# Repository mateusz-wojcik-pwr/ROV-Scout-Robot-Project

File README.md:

# ROV-Scout-Robot-Project
Projekt mobilnego robota zwiadowczego typu ROV realizowany przez studentów kierunku Automatyka i Robotyka na Politechnice Wrocławskiej. Zespół projektowy: Zuzanna Kunikowska, Mateusz Wójcik

# Elektronika
### __Status ukończenia: 70%__
Poniższa sekcja zawiera informacje na temat elektronicznej części projektu. Jest ona podzielona na trzy moduły:

* moduł sterownika robota mobilnego
* moduł sterownika silników robota mobilnego
* moduł zdalnego sterowania (nadajnik)

## Moduł sterownika robota mobilnego
*TBI*

## Moduł sterownika silników robota mobilnego
*TBI*

## Moduł zdalnego sterowania
*TBI*

# Oprogramowanie Embedded
### __Status ukończenia: 50%__
Ta sekcja zawiera informacje na temat rozwiązań w ramach oprogramowania mikrokontrolera zarządzającego robotem. Jest ona podzielona na dwa moduły:

* moduł oprogramowania sterownika robota mobilnego
* moduł oprogramowania nadajnika radiowego

## Oprogramowanie sterownika robota mobilnego
*TBI*

## Oprogramowanie nadajnika
*TBI*

# Konstrukcja mechaniczna
### __Status ukończenia: 40%__
Poniższa sekcja zawiera informacje na temat rozwiązań mechanicznych wykorzystanych przy budowie robota

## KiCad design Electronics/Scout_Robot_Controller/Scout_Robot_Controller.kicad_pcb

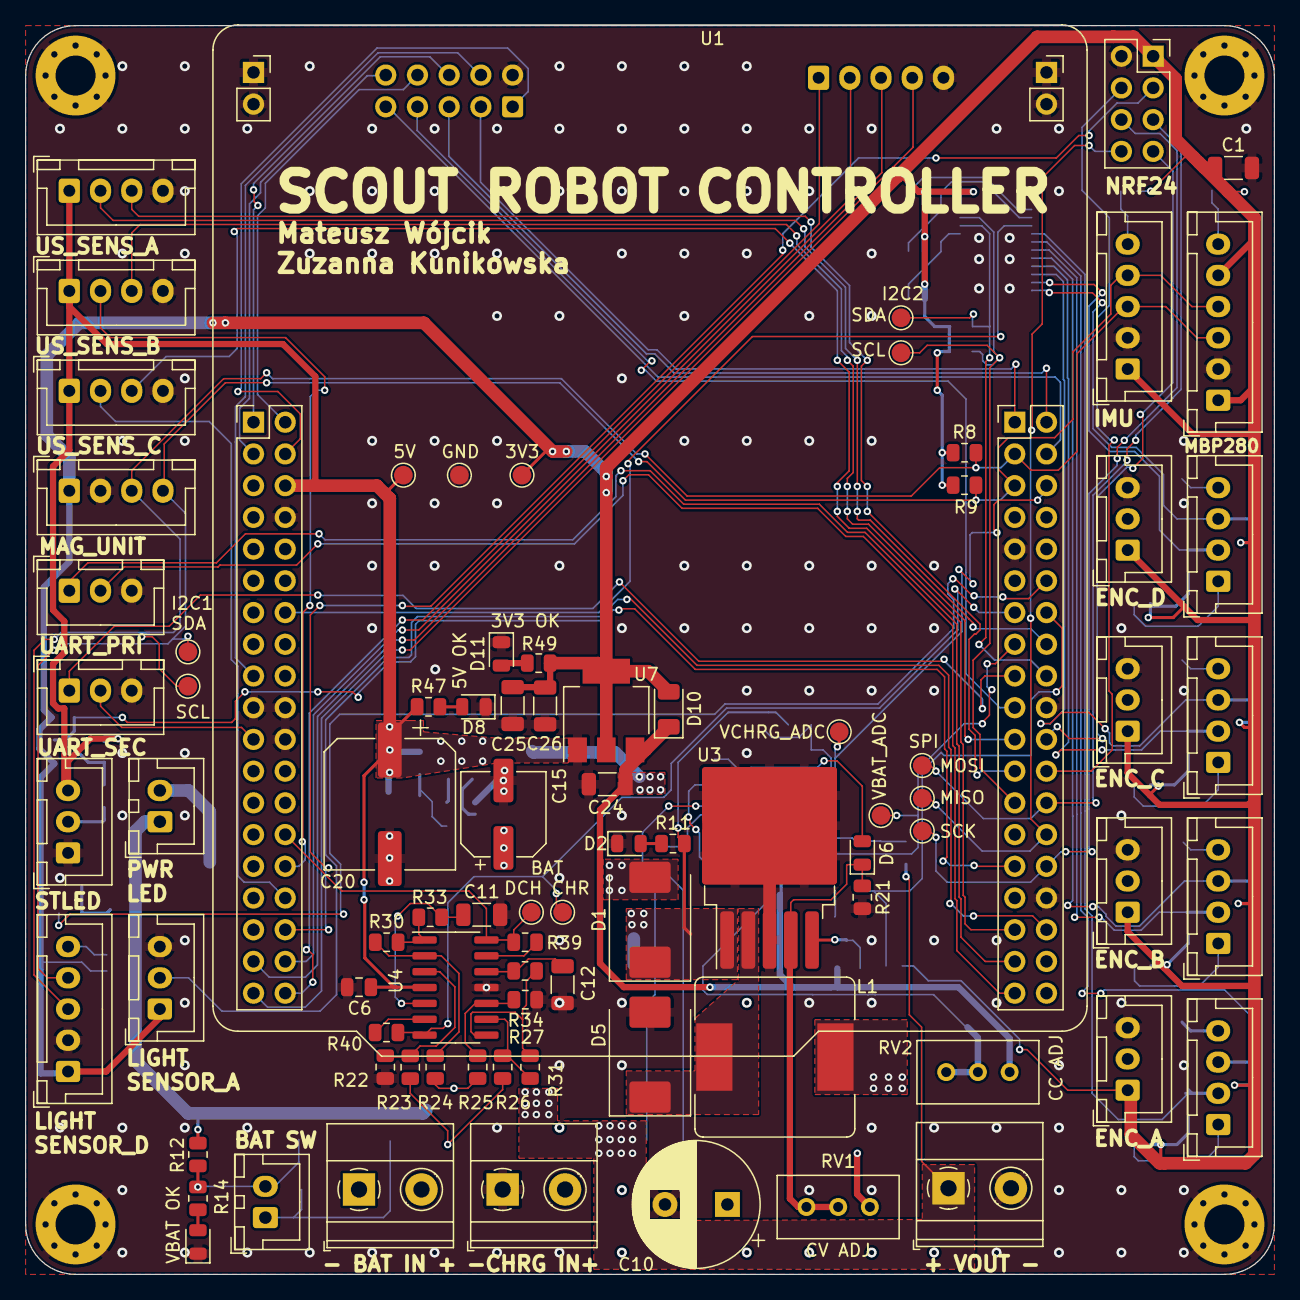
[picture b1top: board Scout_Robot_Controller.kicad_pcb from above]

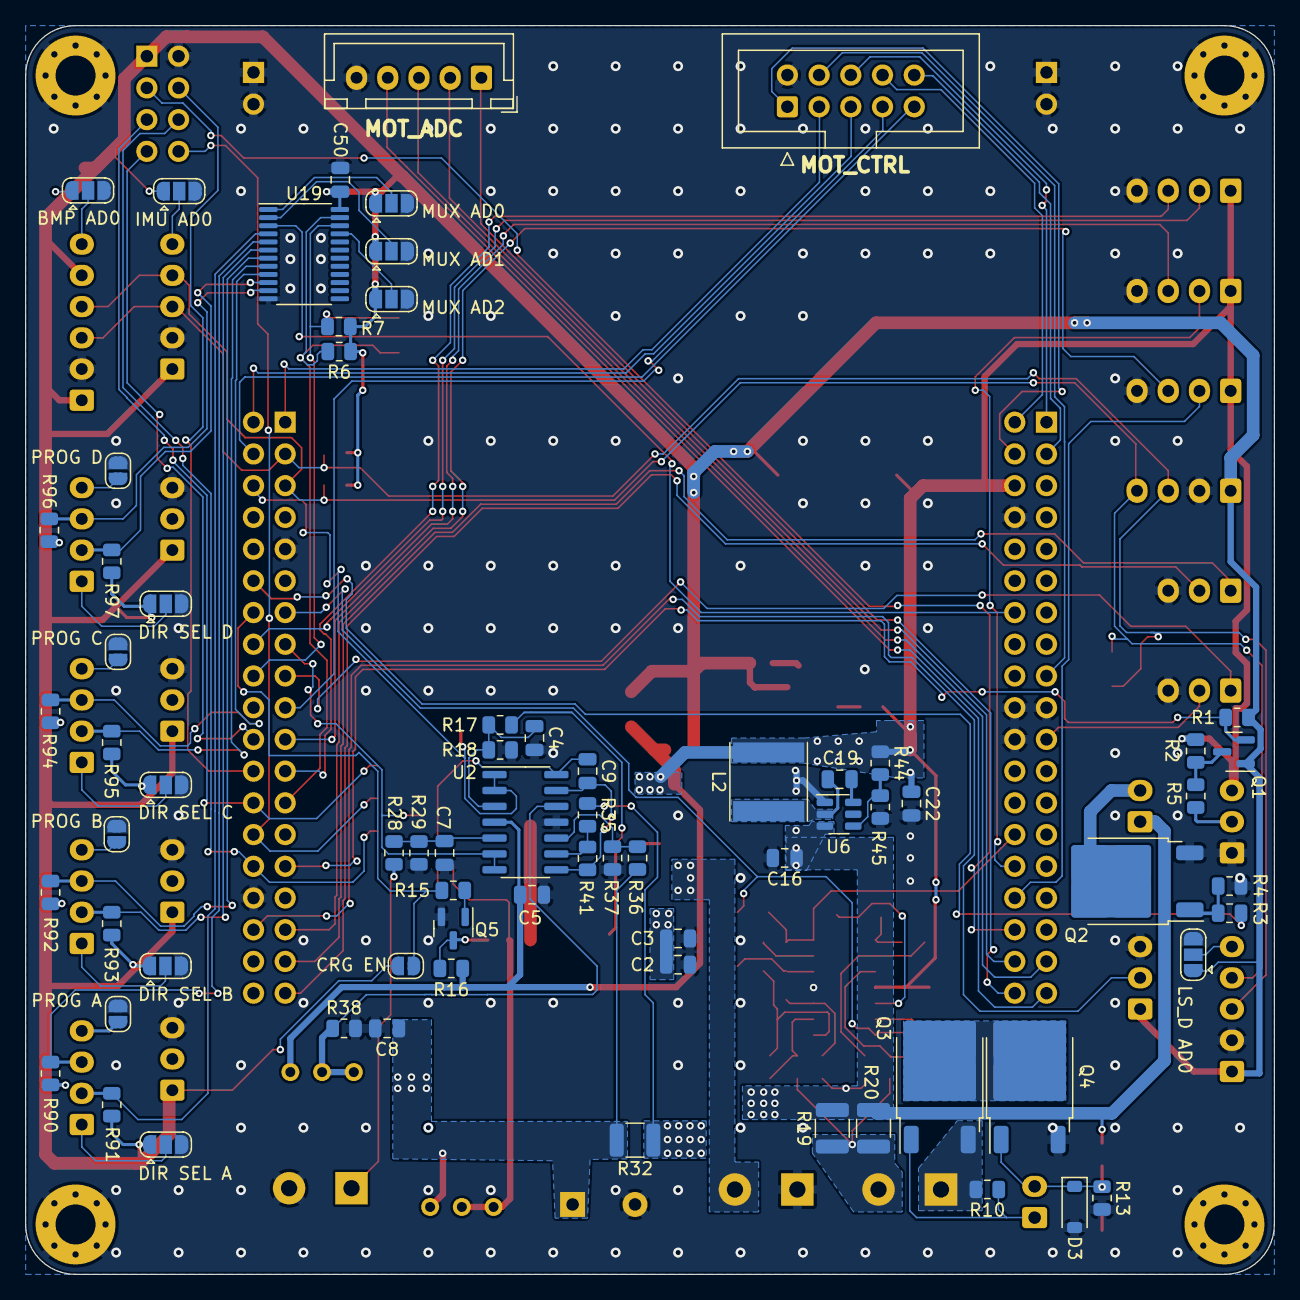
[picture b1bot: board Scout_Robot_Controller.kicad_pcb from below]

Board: 2 copper layers, 100.0 x 100.0 mm, 159 parts (71 on the bottom side), 108 nets.

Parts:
C1, C11, C12, C24, C25, C26: 1u; C_1206_3216Metric
C2, C3, C4, C5, C6, C7, C8, C9, C16, C19, C22, C50: 100n; C_0805_2012Metric
C10: 470u/35V; CP_Radial_D10.0mm_P5.00mm
C15: 47u/35V; CP_Elec_6.3x5.8
C20: 1m/10V; CP_Elec_10x7.9
D1, D5: D_Schottky; D_SMC
D2: V_CHRG_OK; LED_0805_2012Metric
D3: 15V; D_SOD-123
D4: V_BAT_OK; LED_0805_2012Metric
D6: CC_ON; LED_0805_2012Metric
D8: 5V_OK; LED_0805_2012Metric
D10: D; D_1206_3216Metric
D11: 3V3_OK; LED_0805_2012Metric
H1, H2, H3, H4: MH; MountingHole_3.2mm_M3_Pad_Via
J1: ENC_A_COMM; JST_XH_B4B-XH-A_1x04_P2.50mm_Vertical
J2: ENC_C_COMM; JST_XH_B4B-XH-A_1x04_P2.50mm_Vertical
J3: STATUS_LED; JST_XH_B3B-XH-A_1x03_P2.50mm_Vertical
J4: PWR_LEDS; JST_XH_B2B-XH-A_1x02_P2.50mm_Vertical
J5: ENC_A_POW; JST_XH_B3B-XH-A_1x03_P2.50mm_Vertical
J6: ENC_C_POW; JST_XH_B3B-XH-A_1x03_P2.50mm_Vertical
J7: ENC_B_COMM; JST_XH_B4B-XH-A_1x04_P2.50mm_Vertical
J8: ENC_D_COMM; JST_XH_B4B-XH-A_1x04_P2.50mm_Vertical
J9: NRF2401L; PinSocket_2x04_P2.54mm_Vertical
J10: ENC_B_POW; JST_XH_B3B-XH-A_1x03_P2.50mm_Vertical
J11: ENC_D_POW; JST_XH_B3B-XH-A_1x03_P2.50mm_Vertical
J12: LIGHT_SENS_ANALOG; JST_XH_B3B-XH-A_1x03_P2.50mm_Vertical
J13: BMP280_CONN; JST_XH_B6B-XH-A_1x06_P2.50mm_Vertical
J14: UART_PRIM; JST_XH_B3B-XH-A_1x03_P2.50mm_Vertical
J15: UART_SEC; JST_XH_B3B-XH-A_1x03_P2.50mm_Vertical
J16: MAGNETOMETER_CONN; JST_XH_B4B-XH-A_1x04_P2.50mm_Vertical
J17: BAT_OUT; TerminalBlock_Phoenix_MKDS-1,5-2_1x02_P5.00mm_Horizontal
J21: US_SENS_C_CONN; JST_XH_B4B-XH-A_1x04_P2.50mm_Vertical
J22: LS_DIG_CONN; JST_XH_B5B-XH-A_1x05_P2.50mm_Vertical
J23: IMU_CONN; JST_XH_B5B-XH-A_1x05_P2.50mm_Vertical
J24: US_SENS_A_CONN; JST_XH_B4B-XH-A_1x04_P2.50mm_Vertical
J25: US_SENS_B_CONN; JST_XH_B4B-XH-A_1x04_P2.50mm_Vertical
J26: BAT_IN; TerminalBlock_Phoenix_MKDS-1,5-2_1x02_P5.00mm_Horizontal
J27: CHRGR_IN; TerminalBlock_Phoenix_MKDS-1,5-2_1x02_P5.00mm_Horizontal
J28: BAT_SW; JST_XH_B2B-XH-A_1x02_P2.50mm_Vertical
J29: ADC_CURR_CONN; JST_XH_B5B-XH-A_1x05_P2.50mm_Vertical
J30: MOTOR_CONTROL; IDC-Header_2x05_P2.54mm_Vertical
JP1: DIR_SEL_A; SolderJumper-3_P1.3mm_Open_RoundedPad1.0x1.5mm
JP2: DIR_SEL_C; SolderJumper-3_P1.3mm_Open_RoundedPad1.0x1.5mm
JP3: PROG_A; SolderJumper-2_P1.3mm_Open_RoundedPad1.0x1.5mm
JP4: PROG_C; SolderJumper-2_P1.3mm_Open_RoundedPad1.0x1.5mm
JP5: DIR_SEL_B; SolderJumper-3_P1.3mm_Open_RoundedPad1.0x1.5mm
JP6: DIR_SEL_D; SolderJumper-3_P1.3mm_Open_RoundedPad1.0x1.5mm
JP7: PROG_B; SolderJumper-2_P1.3mm_Open_RoundedPad1.0x1.5mm
JP8: PROG_D; SolderJumper-2_P1.3mm_Open_RoundedPad1.0x1.5mm
JP9: BMP280_AD_SEL; SolderJumper-3_P1.3mm_Open_RoundedPad1.0x1.5mm
JP10: LS_DIG_AD_SEL; SolderJumper-3_P1.3mm_Open_RoundedPad1.0x1.5mm
JP11: IMU_AD0_SEL; SolderJumper-3_P1.3mm_Open_RoundedPad1.0x1.5mm
JP12: CHRG_EN_JP; SolderJumper-2_P1.3mm_Open_RoundedPad1.0x1.5mm
JP15: MUX_ADDR_A0; SolderJumper-3_P1.3mm_Open_RoundedPad1.0x1.5mm
JP16: MUX_ADDR_A1; SolderJumper-3_P1.3mm_Open_RoundedPad1.0x1.5mm
JP17: MUX_ADDR_A2; SolderJumper-3_P1.3mm_Open_RoundedPad1.0x1.5mm
L1: 33u/3A; L_Bourns_SRR1260
L2: 3u3/3A; FERROCORE_DJNR6045
Q1: Q_NMOS_GSD; SOT-23
Q2, Q3, Q4: Q_NMOS_GDS; TO-252-2
Q5: Q_NPN_BEC; SOT-23
R1, R2: 2.2k; R_0805_2012Metric
R3, R5, R21, R38: 470R; R_0805_2012Metric
R4, R10, R13, R15: 47k; R_0805_2012Metric
R6, R7, R8, R9, R11, R33, R34, R39, R40, R90, R91, R92, R93, R94, R95, R96, R97: 4k7; R_0805_2012Metric
R12, R18, R23, R24, R25, R26, R29: 1k; R_0805_2012Metric
R14: 2k2; R_0805_2012Metric
R16, R17, R27, R28, R31, R35, R36, R37, R41, R45: 10k; R_0805_2012Metric
R19, R20, R32: 50m; R_1210_3225Metric
R22, R30: 33k; R_0805_2012Metric
R44: 56k; R_0805_2012Metric
R47: 680R; R_0805_2012Metric
R49: 220R; R_0805_2012Metric
RV1, RV2: 10k; Potentiometer_Bourns_3296W_Vertical
TP3: SPI_SCK_TP; TestPoint_Pad_D1.5mm
TP4: SPI_MISO_TP; TestPoint_Pad_D1.5mm
TP5: SPI_MOSI_TP; TestPoint_Pad_D1.5mm
TP6: I2C1_SDA_TP; TestPoint_Pad_D1.5mm
TP7: I2C1_SCL_TP; TestPoint_Pad_D1.5mm
TP8: I2C2_SDA_TP; TestPoint_Pad_D1.5mm
TP9: I2C2_SCL_TP; TestPoint_Pad_D1.5mm
TP12: VCHRG_ADC_TP; TestPoint_Pad_D1.5mm
TP13: VBAT_ADC_TP; TestPoint_Pad_D1.5mm
TP14: GND_TP; TestPoint_Pad_D1.5mm
TP15: BAT_CURR_DISCHRG_TP; TestPoint_Pad_D1.5mm
TP16: BAT_CURR_CHRG_TP; TestPoint_Pad_D1.5mm
TP18: 5V_TP; TestPoint_Pad_D1.5mm
TP21: 3V3_TP; TestPoint_Pad_D1.5mm
U1: NUCLEO64-L476; ST_Morpho_Connector_64_STLink
U2, U4: LM324; SOIC-14_3.9x8.7mm_P1.27mm
U3: LM2596S-ADJ; TO-263-5_TabPin3
U6: AP62300TWU; TSOT-23-6
U7: AP1117-33; SOT-223-3_TabPin2
U19: TCA9548APWR; TSSOP-24_4.4x7.8mm_P0.65mm

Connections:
+3V3: C1.1, C25.1, C26.1, C50.1, D10.2 (A), J5.1, J6.1, J9.1, J10.1, J11.1, J12.1, J13.1, J13.5, J16.1, J22.1, J23.1, JP1.1 (A), JP2.1 (A), JP5.1 (A), JP6.1 (A), JP9.1 (A), JP10.1 (A), JP11.1 (A), JP12.2 (B), JP15.1 (A), JP16.1 (A), JP17.1 (A), Q1.1 (G), R1.1, R6.1, R7.1, R8.1, R9.1, R49.1, R90.1, R91.1, R92.1, R93.1, R94.1, R95.1, R96.1, R97.1, TP21.1, U7.2 (VO), U19.24 (VCC)
+5V: C5.1, C6.1, C20.1, C22.1, C24.1, D10.1 (K), J3.3, J21.1, J24.1, J25.1, L2.2, R2.1, R16.2, R44.1, R47.1, RV2.1, TP18.1, U1.6 (E5V), U2.4 (V+), U4.4 (V+), U7.3 (VI)
/BatteryManagement/BAT+: J26.2, R19.1, R20.1, R23.1, R26.1
/BatteryManagement/BAT-: J26.1, Q3.3 (S), R10.2
/BatteryManagement/BAT_SW_A: J28.1, Q3.1 (G), R10.1
/BatteryManagement/BAT_SW_B: D3.1 (K), J28.2, Q4.1 (G), R12.2, R13.1, R14.1
/BatteryManagement/V_CHRG: C2.1, C3.1, D1.1 (K), R11.2, R17.1, U3.1 (VIN)
/BatteryManagement/V_CHRGR: D1.2 (A), J27.2
/I2C2MUX/A0: JP15.2 (C), U19.1 (A0)
/I2C2MUX/A1: JP16.2 (C), U19.2 (A1)
/I2C2MUX/A2: JP17.2 (C), U19.21 (A2)
BAT_CURR_CHRG_ADC: R39.1, TP16.1, U1.28 (PA0), U4.14
BAT_CURR_DISCH_ADC: R40.1, TP15.1, U1.51 (PA6), U4.7
CHRG_EN: JP12.1 (A), R15.1, U1.52 (PA11)
ENC_A_SCL: J1.3, R90.2, U19.5 (SC0)
ENC_A_SDA: J1.2, R91.2, U19.4 (SD0)
ENC_B_SCL: J7.3, R92.2, U19.7 (SC1)
ENC_B_SDA: J7.2, R93.2, U19.6 (SD1)
ENC_C_SCL: J2.3, R94.2, U19.9 (SC2)
ENC_C_SDA: J2.2, R95.2, U19.8 (SD2)
ENC_D_SCL: J8.3, R96.2, U19.11 (SC3)
ENC_D_SDA: J8.2, R97.2, U19.10 (SD3)
GND: C1.2, C2.2, C3.2, C4.2, C5.2, C6.2, C7.2, C8.2, C10.2, C11.2, C12.2, C15.2, C16.2, C20.2, C22.2, C24.2, C25.2, C26.2, C50.2, D2.1 (K), D3.2 (A), D4.1 (K), D5.2 (A), D8.1 (K), D11.1 (K), H1.1, H2.1, H3.1, H4.1, J3.1, J5.3, J6.3, J9.2, J10.3, J11.3, J12.3, J13.2, J14.3, J15.3, J16.2, J17.2, J21.4, J22.2, J23.2, J24.4, J25.4, J27.1, J29.5, J30.2, JP1.3 (B), JP2.3 (B), JP3.1 (A), JP4.1 (A), JP5.3 (B), JP6.3 (B), JP7.1 (A), JP8.1 (A), JP9.3 (B), JP10.3 (B), JP11.3 (B), JP15.3 (B), JP16.3 (B), JP17.3 (B), Q2.3 (S), Q4.3 (S), Q5.2 (E), R4.1, R13.2, R18.2, R21.2, R22.1, R27.2, R29.2, R37.2, R38.2, R45.2, TP14.1, U1.8 (GND), U1.19 (GND), U1.20 (GND), U1.22 (GND), U1.47 (GND), U1.58 (GND), U1.70 (AGND), U1.77 (GND), U1.78 (GND), U1.79 (GND), U1.80 (GND), U2.11 (V-), U3.3 (GND), U4.11 (V-), U6.1 (GND), U7.1 (GND), U19.12 (GND)
I2C_1_SCL: J13.3, J16.3, J22.3, J23.3, R8.2, TP7.1, U1.41 (PB8)
I2C_1_SDA: J13.4, J16.4, J22.4, J23.4, R9.2, TP6.1, U1.43 (PB9)
I2C_2_SCL: R6.2, TP9.1, U1.63 (PB10), U19.23 (SDA)
I2C_2_SDA: R7.2, TP8.1, U1.56 (PB11), U19.22 (SCL)
LIGHT_SENS_ADC: J12.2, U1.72 (PC4)
MOT_A_CURR_ADC: J29.1, U1.38 (PC0)
MOT_A_DIR: J30.10, U1.3 (PC12)
MOT_A_PWM: J30.9, U1.42 (PC6)
MOT_B_CURR_ADC: J29.2, U1.36 (PC1)
MOT_B_DIR: J30.8, U1.2 (PC11)
MOT_B_PWM: J30.7, U1.57 (PC7)
MOT_C_CURR_ADC: J29.3, U1.35 (PC2)
MOT_C_DIR: J30.6, U1.1 (PC10)
MOT_C_PWM: J30.5, U1.40 (PC8)
MOT_D_CURR_ADC: J29.4, U1.37 (PC3)
MOT_D_DIR: J30.4, U1.17 (PA15)
MOT_D_PWM: J30.3, U1.39 (PC9)
MOT_EN: J30.1, U1.4 (PD2)
NRF_CE: J9.4, U1.62 (PB1)
NRF_CSN: J9.3, U1.34 (PB0)
NRF_IRQ: J9.7, U1.60 (PB2)
unnamed: C8.1, C10.1, L1.2, R32.2, R36.1, RV1.1
unnamed: D2.2 (A), R11.1
unnamed: D4.2 (A), R14.2
unnamed: D5.1 (K), L1.1, U3.2 (OUT)
unnamed: C9.1, D6.2 (A), U2.14
unnamed: D6.1 (K), R21.1, RV1.2, RV1.3, U3.4 (FB)
unnamed: D8.2 (A), R47.2
unnamed: D11.2 (A), R49.2
unnamed: J1.1, JP1.2 (C)
unnamed: J1.4, JP3.2 (B)
unnamed: J2.1, JP2.2 (C)
unnamed: J2.4, JP4.2 (B)
unnamed: J3.2, R5.2
unnamed: J4.2, Q2.2 (D)
unnamed: J7.1, JP5.2 (C)
unnamed: J7.4, JP7.2 (B)
unnamed: J8.1, JP6.2 (C)
unnamed: J8.4, JP8.2 (B)
unnamed: J13.6, JP9.2 (C)
unnamed: J22.5, JP10.2 (C)
unnamed: J23.5, JP11.2 (C)
unnamed: Q1.3 (D), R2.2, R5.1
unnamed: Q2.1 (G), R3.1, R4.2
unnamed: Q3.2 (D), Q4.2 (D)
unnamed: Q5.1 (B), R15.2
unnamed: Q5.3 (C), R16.1, U3.5 (~ON/OFF)
unnamed: R30.2, R33.2, U4.1
unnamed: R31.2, R34.2, U4.8
unnamed: C4.1, R17.2, R18.1, U2.3 (+)
unnamed: C7.1, R28.2, R29.1, U2.5 (+)
unnamed: R36.2, R37.1, U2.10 (+)
unnamed: R35.2, R41.1, U2.9 (-)
unnamed: R38.1, RV2.2, RV2.3, U2.12 (+)
unnamed: C9.2, R41.2, U2.8, U2.13 (-)
unnamed: R22.2, R23.2, U4.3 (+)
unnamed: R24.2, R30.1, U4.2 (-)
unnamed: C11.1, R33.1, U4.5 (+)
unnamed: R40.2, U4.6 (-)
unnamed: R25.2, R27.1, U4.10 (+)
unnamed: R26.2, R31.1, U4.9 (-)
unnamed: C12.1, R34.1, U4.12 (+)
unnamed: R39.2, U4.13 (-)
unnamed: C19.1, U6.6 (BST)
unnamed: R44.2, R45.1, U6.4 (FB)
unnamed: C19.2, L2.1, U6.2 (SW)
PWR_LEDS: R3.2, U1.50 (PA12)
SPI_MISO: J9.8, TP4.1, U1.66 (PB14)
SPI_MOSI: J9.5, TP5.1, U1.64 (PB15)
SPI_SCK: J9.6, TP3.1, U1.68 (PB13)
SYS_RST: U1.14 (~RESET), U19.3 (~RESET)
UART_PRI_RX: J14.2, U1.75 (STLINK_UART_RX/PA3)
UART_PRI_TX: J14.1, U1.73 (STLINK_UART_TX/PA2)
UART_SEC_RX: J15.2, U1.21 (PB7)
UART_SEC_TX: J15.1, U1.55 (PB6)
US_SENS_A_ECHO: J24.3, U1.61 (PA8)
US_SENS_A_TRIG: J24.2, U1.54 (PB12)
US_SENS_B_ECHO: J25.3, U1.59 (PA9)
US_SENS_B_TRIG: J25.2, U1.30 (PA1)
US_SENS_C_ECHO: J21.3, U1.71 (PA10)
US_SENS_C_TRIG: J21.2, U1.32 (PA4)
VCC: C15.1, C16.1, J4.1, J17.1, R12.1, R19.2, R20.2, R24.1, R25.1, R28.1, R32.1, R35.1, U6.3 (IN)
V_BAT_ADC: TP13.1, U1.53 (PA7), U2.6 (-), U2.7
V_CHRGR_ADC: TP12.1, U1.44 (PC5), U2.1, U2.2 (-)
WSLED_DIN: Q1.2 (S), R1.2, U1.67 (PB5)

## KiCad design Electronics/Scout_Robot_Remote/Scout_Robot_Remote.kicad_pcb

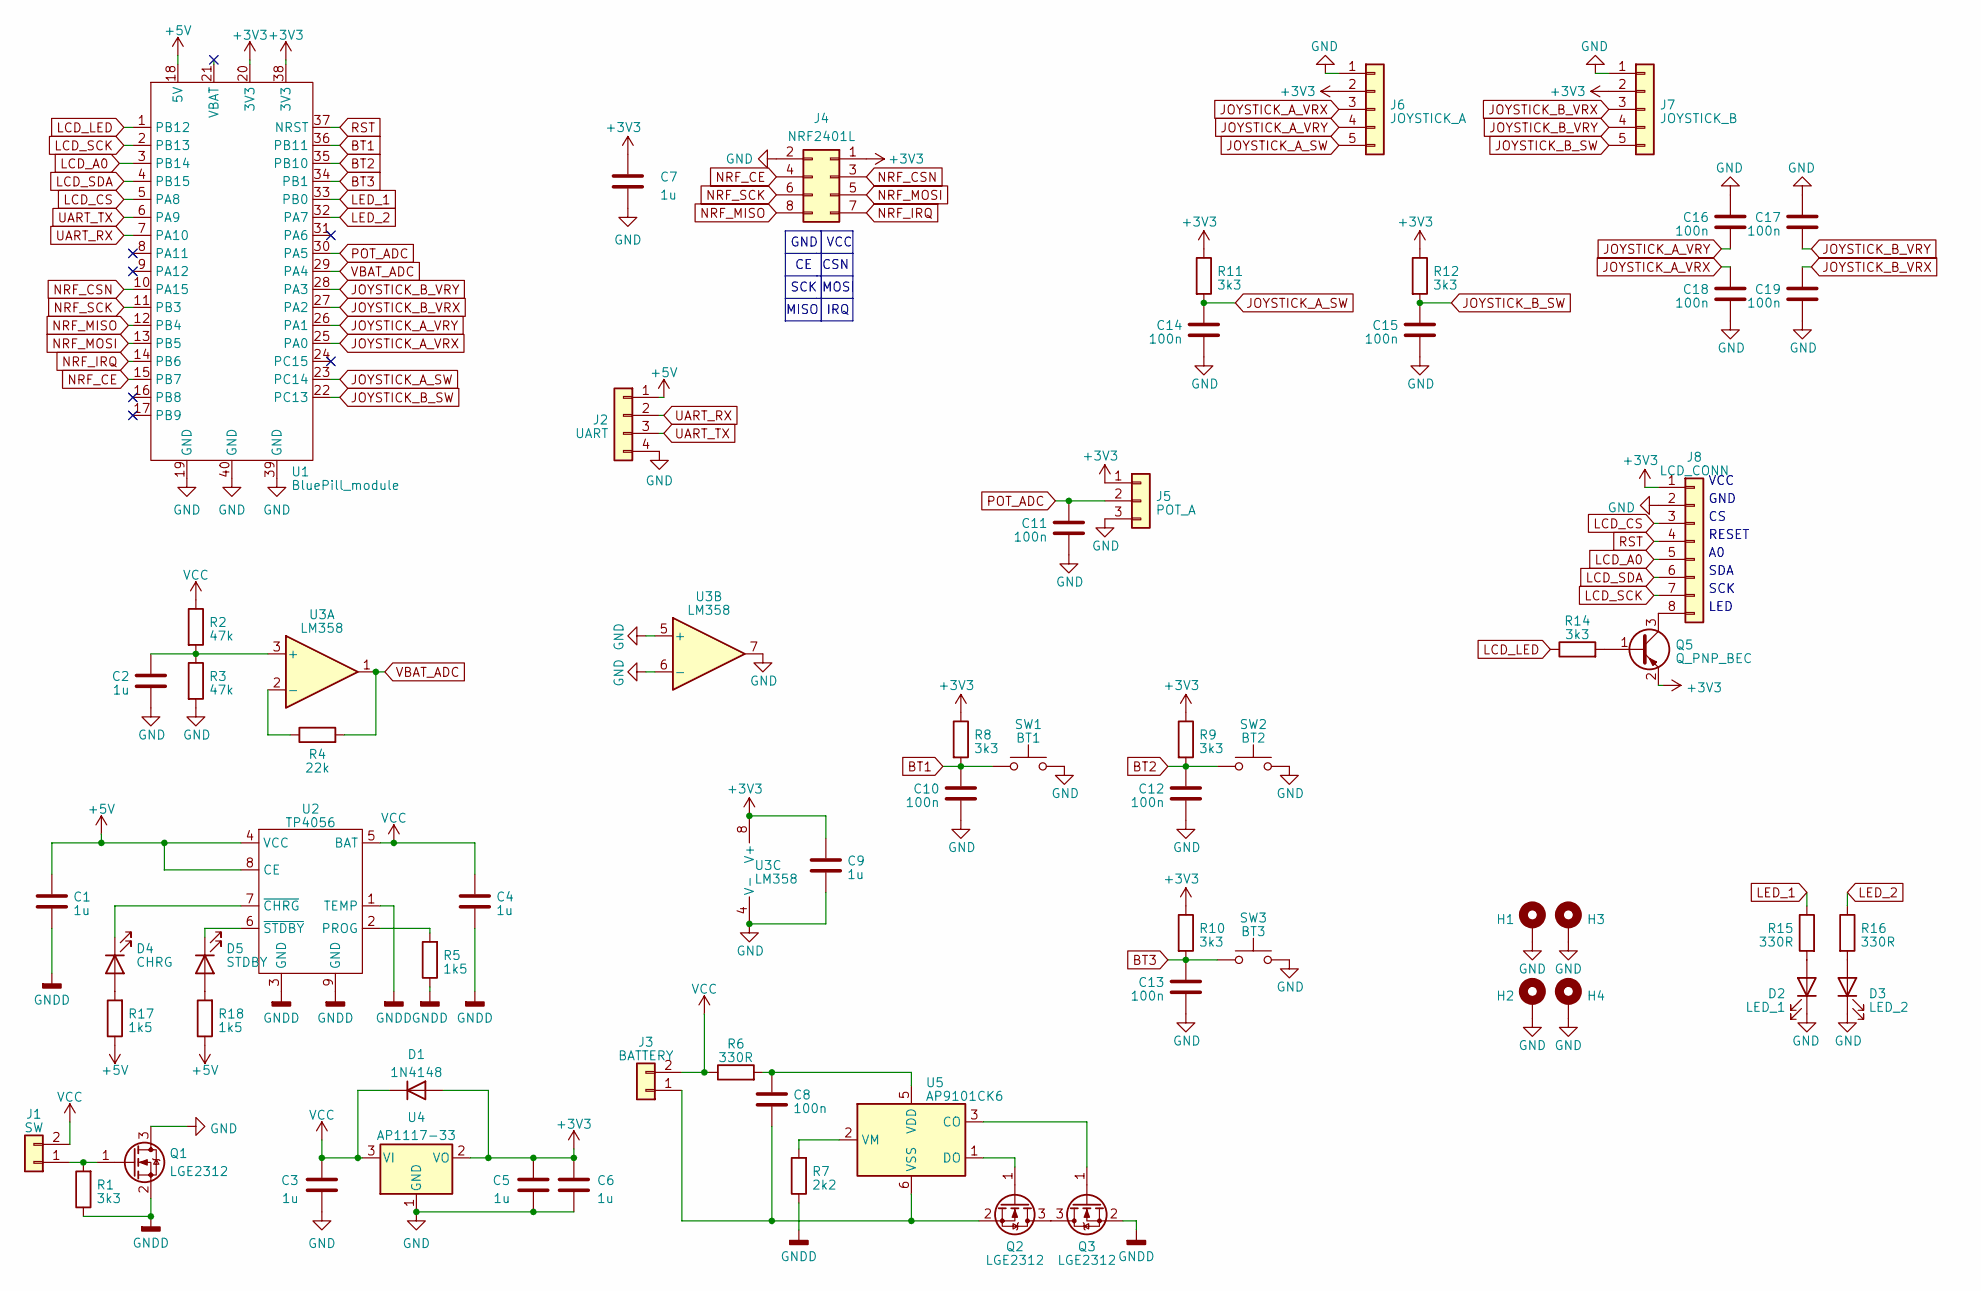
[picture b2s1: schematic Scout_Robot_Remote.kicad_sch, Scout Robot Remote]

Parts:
C1, C2, C3, C4, C5, C6, C7, C9: 1u; C_1206_3216Metric
C8, C10, C11, C12, C13, C14, C15, C16, C17, C18, C19: 100n; C_0805_2012Metric
D1: D; D_1206_3216Metric; MPN 1N4148
D2: LED_1; LED_D3.0mm
D3: LED_2; LED_D3.0mm
D4: CHRG; LED_D3.0mm
D5: STDBY; LED_D3.0mm
H1, H2, H3, H4: MH; MountingHole_3.2mm_M3_Pad_Via
J1: SW; JST_PH_B2B-PH-K_1x02_P2.00mm_Vertical
J2: UART; JST_XH_B4B-XH-A_1x04_P2.50mm_Vertical
J3: BATTERY; JST_XH_B2B-XH-A_1x02_P2.50mm_Vertical
J4: NRF2401L; PinSocket_2x04_P2.54mm_Vertical
J5: POT_A; JST_PH_B3B-PH-K_1x03_P2.00mm_Vertical
J6: JOYSTICK_A; JST_PH_B5B-PH-K_1x05_P2.00mm_Vertical
J7: JOYSTICK_B; JST_PH_B5B-PH-K_1x05_P2.00mm_Vertical
J8: LCD_CONN; PinSocket_1x08_P2.54mm_Vertical
Q1, Q2, Q3: Q_NMOS_GSD; SOT-23; MPN LGE2312
Q5: Q_PNP_BEC; SOT-23
R1, R8, R9, R10, R11, R12, R14: 3k3; R_0805_2012Metric
R2, R3: 47k; R_0805_2012Metric
R4: 22k; R_0805_2012Metric
R5, R17, R18: 1k5; R_0805_2012Metric
R6, R15, R16: 330R; R_0805_2012Metric
R7: 2k2; R_0805_2012Metric
SW1: BT1; SW_Tactile_SPST_Angled_PTS645Vx39-2LFS
SW2: BT2; SW_Tactile_SPST_Angled_PTS645Vx39-2LFS
SW3: BT3; SW_PUSH_6mm_H7.3mm
U1: BluePill_module; BluePill_Module
U2: TP4056; SOIC-8-1EP_3.9x4.9mm_P1.27mm_EP2.41x3.81mm
U3: LM358; SOIC-8_3.9x4.9mm_P1.27mm
U4: AP1117-33; SOT-223-3_TabPin2
U5: AP9101CK6; SOT-23-6

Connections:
+3V3: C5.1, C6.1, C7.1, C9.2, D1.2 (A), J4.1, J5.1, J6.2, J7.2, J8.1, Q5.2 (E), R8.1, R9.1, R10.1, R11.1, R12.1, U1.20 (3V3), U1.38 (3V3), U3.8 (V+), U4.2 (VO)
+5V: C1.2, J2.1, R17.1, R18.1, U1.18 (5V), U2.4 (VCC), U2.8 (CE)
BT1: C10.1, R8.2, SW1.1, U1.36 (PB11)
BT2: C12.1, R9.2, SW2.1, U1.35 (PB10)
BT3: C13.1, R10.2, SW3.1, U1.34 (PB1)
GND: C2.1, C3.2, C5.2, C6.2, C7.2, C9.1, C10.2, C11.2, C12.2, C13.2, C14.2, C15.2, C16.1, C17.1, C18.2, C19.2, D2.1 (K), D3.1 (K), H1.1, H2.1, H3.1, H4.1, J2.4, J4.2, J5.3, J6.1, J7.1, J8.2, Q1.3 (D), R3.2, SW1.2, SW2.2, SW3.2, U1.19 (GND), U1.39 (GND), U1.40 (GND), U3.4 (V-), U3.5 (+), U3.6 (-), U3.7, U4.1 (GND)
GNDD: C1.1, C4.1, Q1.2 (S), Q3.2 (S), R1.1, R5.1, R7.1, U2.1 (TEMP), U2.3 (GND), U2.9 (GND)
JOYSTICK_A_SW: C14.1, J6.5, R11.2, U1.23 (PC14)
JOYSTICK_A_VRX: C18.1, J6.3, U1.25 (PA0)
JOYSTICK_A_VRY: C16.2, J6.4, U1.26 (PA1)
JOYSTICK_B_SW: C15.1, J7.5, R12.2, U1.22 (PC13)
JOYSTICK_B_VRX: C19.1, J7.3, U1.27 (PA2)
JOYSTICK_B_VRY: C17.2, J7.4, U1.28 (PA3)
LCD_A0: J8.5, U1.3 (PB14)
LCD_CS: J8.3, U1.5 (PA8)
LCD_LED: R14.1, U1.1 (PB12)
LCD_SCK: J8.7, U1.2 (PB13)
LCD_SDA: J8.6, U1.4 (PB15)
LED_1: R15.1, U1.33 (PB0)
LED_2: R16.1, U1.32 (PA7)
NRF_CE: J4.4, U1.15 (PB7)
NRF_CSN: J4.3, U1.10 (PA15)
NRF_IRQ: J4.7, U1.14 (PB6)
NRF_MISO: J4.8, U1.12 (PB4)
NRF_MOSI: J4.5, U1.13 (PB5)
NRF_SCK: J4.6, U1.11 (PB3)
unnamed: D2.2 (A), R15.2
unnamed: D3.2 (A), R16.2
unnamed: D4.2 (A), R17.2
unnamed: D4.1 (K), U2.7 (~CHRG)
unnamed: D5.2 (A), R18.2
unnamed: D5.1 (K), U2.6 (~STDBY)
unnamed: J1.1, Q1.1 (G), R1.2
unnamed: C8.1, J3.1, Q2.2 (S), U5.6 (VSS)
unnamed: J8.8, Q5.3 (C)
unnamed: Q2.3 (D), Q3.3 (D)
unnamed: Q2.1 (G), U5.1 (DO)
unnamed: Q3.1 (G), U5.3 (CO)
unnamed: Q5.1 (B), R14.2
unnamed: R5.2, U2.2 (PROG)
unnamed: C2.2, R2.2, R3.1, U3.3 (+)
unnamed: R4.1, U3.2 (-)
unnamed: C8.2, R6.2, U5.5 (VDD)
unnamed: R7.2, U5.2 (VM)
POT_ADC: C11.1, J5.2, U1.30 (PA5)
RST: J8.4, U1.37 (NRST)
UART_RX: J2.2, U1.7 (PA10)
UART_TX: J2.3, U1.6 (PA9)
VBAT_ADC: R4.2, U1.29 (PA4), U3.1
VCC: C3.1, C4.2, D1.1 (K), J1.2, J3.2, R2.1, R6.1, U2.5 (BAT), U4.3 (VI)

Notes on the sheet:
IRQ
SCK
MISO
RESET
SDA
GND
VCC
MOSI
CSN
LED

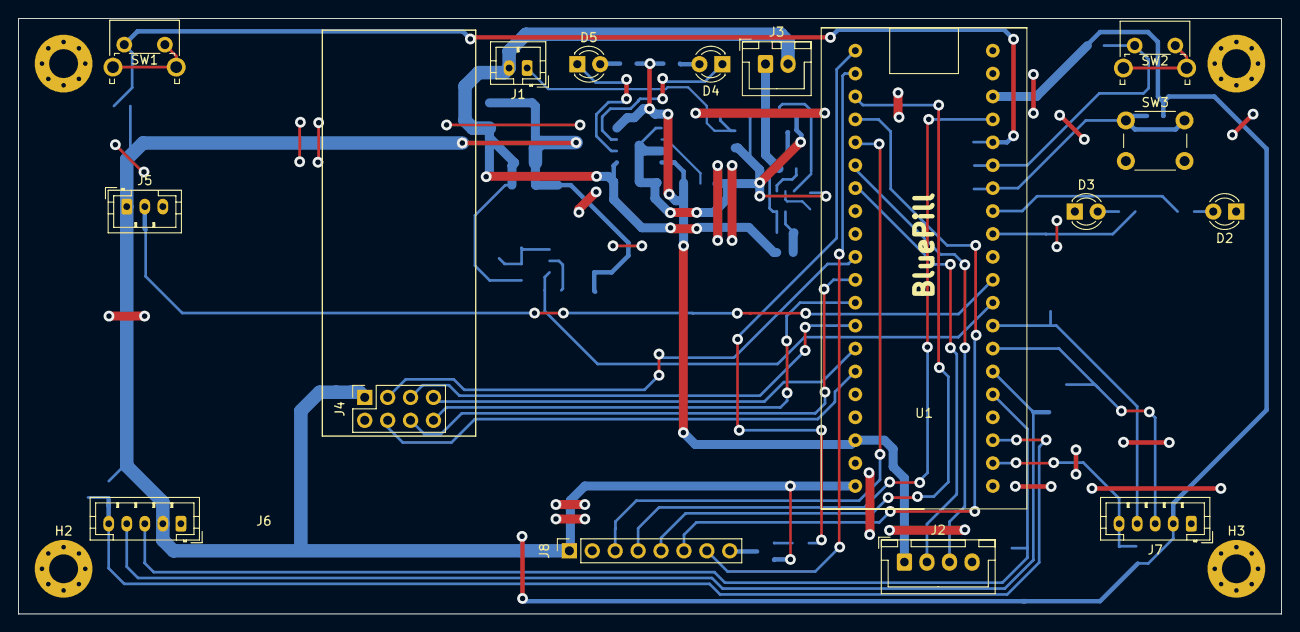
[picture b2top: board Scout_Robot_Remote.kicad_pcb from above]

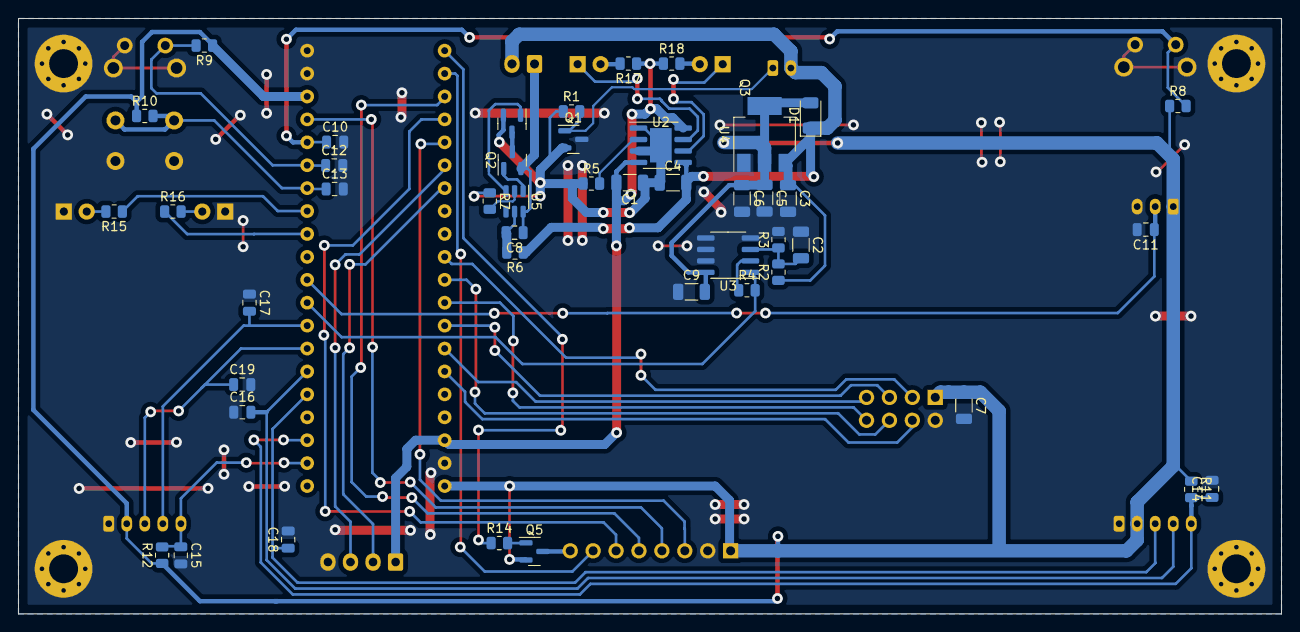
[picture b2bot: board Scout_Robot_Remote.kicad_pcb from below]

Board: 2 copper layers, 140.0 x 66.0 mm, 65 parts (45 on the bottom side), 50 nets.
